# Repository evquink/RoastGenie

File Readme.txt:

RoastGenie

This project documents enhancements to the control system in the GeneCafe
Coffee roaster.  It adds PID control, batch label printing, data collection
and processing, and bean mass temperature measurement.

Folders in this repository

* Documentation
Various documentation files covering system design and operation of the
system.

* HeaterInterface
Eagle schematics and board files for hardware that controls the 120v heater.

* PlotGenieSW 
Files required to process the data files from the plot genie using a python
script and gnuplot.

* RoasterInterface
Eagle schematics and board files for hardware that interfaces the Diavolino to
the modified coffee roaster.

* RoastGeniePanel
2-D drawing file for the panel on the RoastGenie Controller.

* RoastGenieSW_Diavolino
Arduino files for the program that runs on the Diavolino for executing primary
roaster control.

* RoastGenieSW_ProTrinket
Arduino files for the program that runs on the ProTrinket for capturing bean
mass temperature.

* RoastGenieSW_RasPi
The Python script that does the data acquisition and file management for the
RoastGenie

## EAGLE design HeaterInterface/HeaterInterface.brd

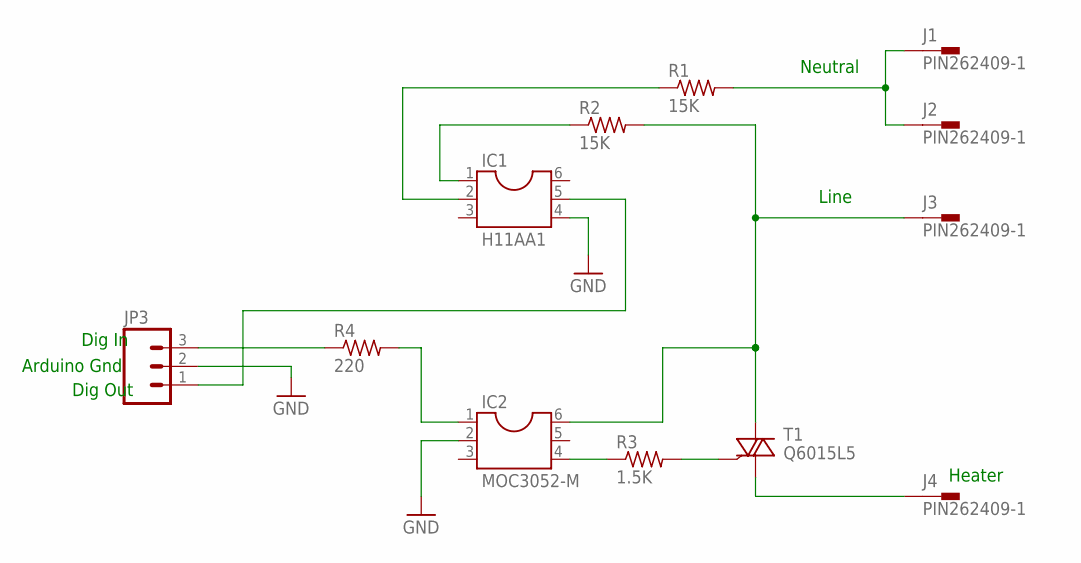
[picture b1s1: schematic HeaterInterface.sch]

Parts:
IC1: H11AA1; DIL06
IC2: MOC3052-M; DIL06
J1, J2, J3, J4: PIN262409-1; 62409-1
JP3: M03PTH; 1X03
R1, R2: 15K; 0207/10
R3: 1.5K; 0207/10
R4: 220; 0207/10
T1: Q6015L5; TO220BH

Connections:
GND: IC1.4, IC2.2, JP3.2
unnamed: IC1.5, JP3.1
unnamed: IC1.2, R1.1
unnamed: IC1.1, R2.1
unnamed: IC2.6, J3.A1 (1), R2.2, T1.T2 (A2)
unnamed: JP3.3, R4.1
unnamed: IC2.1, R4.2
unnamed: IC2.4, R3.1
unnamed: R3.2, T1.G
unnamed: J4.A1 (1), T1.T1 (A1)
NEUTRAL: J1.A1 (1), J2.A1 (1), R1.2

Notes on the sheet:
Dig Out
Dig In
Arduino Gnd
Neutral
Line
Heater

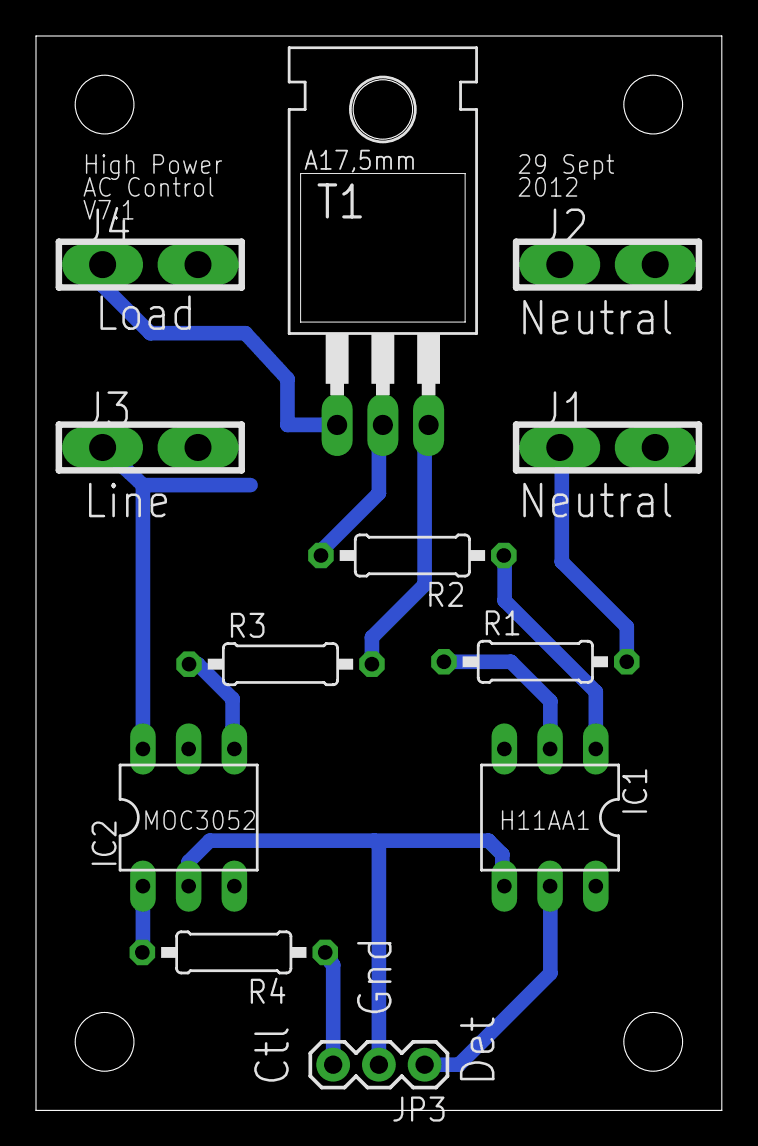
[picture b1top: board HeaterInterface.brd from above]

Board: 2 copper layers, 38.1 x 59.7 mm, 12 parts (0 on the bottom side), 11 nets.

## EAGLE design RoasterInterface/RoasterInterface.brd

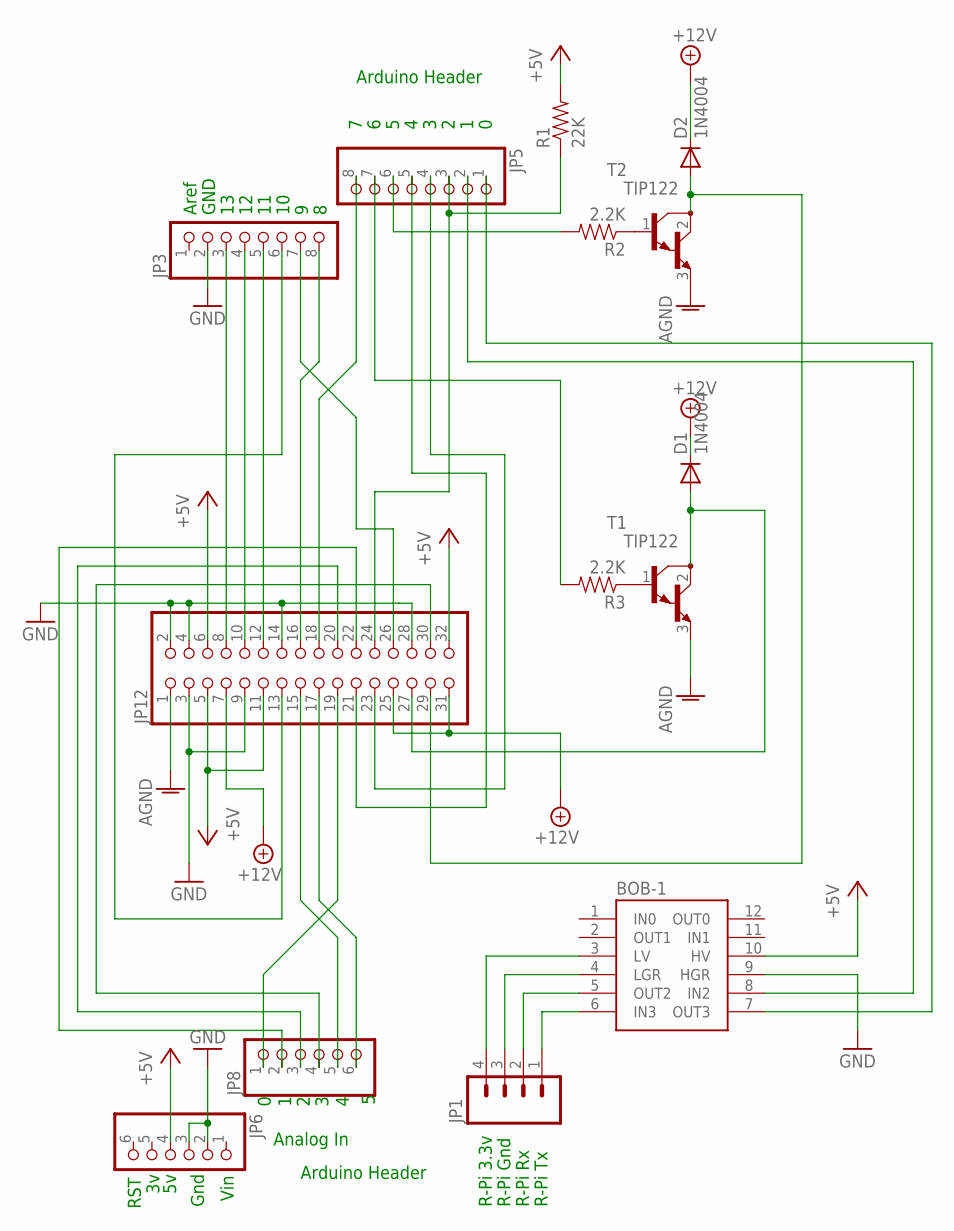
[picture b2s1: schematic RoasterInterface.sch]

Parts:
BOB-1: BOB-08745DEFAULT; 5X6BOB
D1, D2: 1N4004; DO41-10
JP1: M04LOCK; 1X04_LOCK
JP3, JP5: PINHD-1X8CLEANBIG; 1X08-CLEANBIG
JP6, JP8: PINHD-1X6CB; 1X06-CLEANBIG
JP12: PINHD-2X16; 2X16
R1: 22K; AXIAL-0.4
R2, R3: 2.2K; AXIAL-0.4
T1, T2: TIP122; TO220

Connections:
+5V: BOB-1.10 (HV), JP6.4, JP12.5, JP12.6, JP12.11, JP12.32, R1.P$2 (2)
+12V: D1.C, D2.C, JP12.7, JP12.25, JP12.31
AGND: JP12.1, T1.3 (E), T2.3 (E)
ARD-RX: BOB-1.7 (OUT3), JP5.1
GND: BOB-1.9 (HGR), JP3.2, JP6.2, JP6.3, JP12.2, JP12.3, JP12.4, JP12.9, JP12.14, JP12.28
unnamed: R2.P$1 (1), T2.1 (B)
unnamed: JP3.7, JP12.26
unnamed: JP5.5, JP12.21
unnamed: JP3.8, JP12.16
unnamed: JP5.7, R3.P$2 (2)
unnamed: JP5.8, JP12.18
unnamed: JP3.5, JP12.12
unnamed: JP3.6, JP12.13
unnamed: JP5.6, R2.P$2 (2)
unnamed: JP8.1, JP12.19
unnamed: JP8.5, JP12.15
unnamed: JP3.4, JP12.10
unnamed: R3.P$1 (1), T1.1 (B)
unnamed: JP3.3, JP12.8
unnamed: JP8.6, JP12.17
unnamed: JP8.2, JP12.22
unnamed: JP8.3, JP12.20
unnamed: JP8.4, JP12.30
unnamed: JP5.3, JP12.24, R1.P$1 (1)
unnamed: BOB-1.8 (IN2), JP5.2
unnamed: BOB-1.4 (LGR), JP1.3
unnamed: BOB-1.3 (LV), JP1.4
unnamed: BOB-1.5 (OUT2), JP1.2
unnamed: BOB-1.6 (IN3), JP1.1
unnamed: JP5.4, JP12.23
unnamed: D2.A, JP12.29, T2.2 (C)
unnamed: D1.A, JP12.27, T1.2 (C)

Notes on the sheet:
Arduino Header
Analog In
Vin
Gnd
RST
GND
Aref
R-Pi Gnd
R-Pi 3.3v
R-Pi Rx
R-Pi Tx

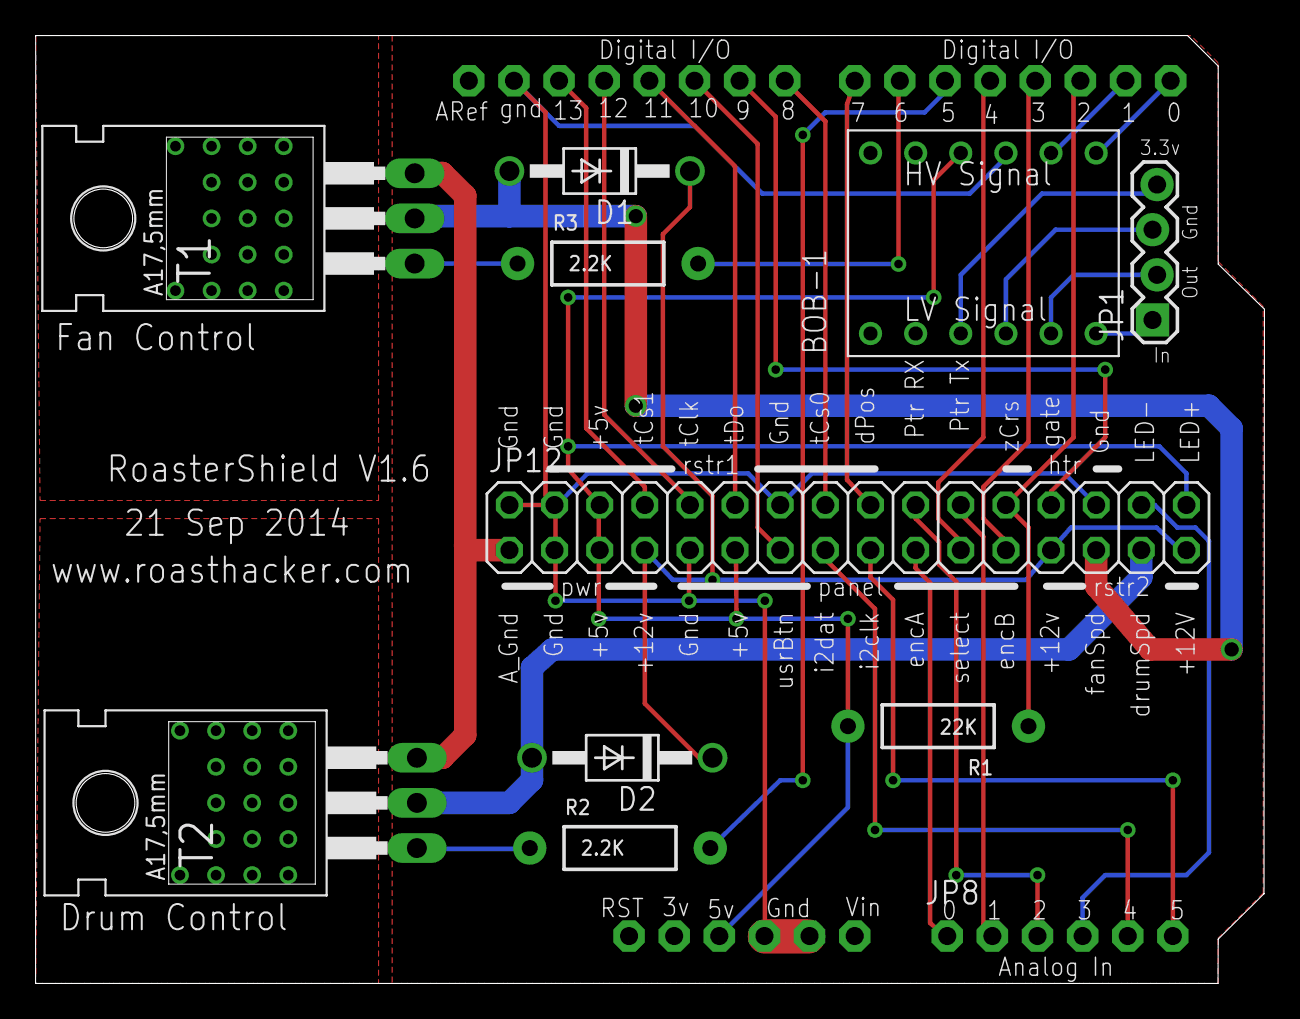
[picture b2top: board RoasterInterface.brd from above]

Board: 2 copper layers, 69.2 x 53.4 mm, 14 parts (0 on the bottom side), 32 nets.

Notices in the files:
parts and their libraries:
SparkFun: Licensing: CC v3.0 Share-Alike You are welcome to use this library for commercial purposes.
